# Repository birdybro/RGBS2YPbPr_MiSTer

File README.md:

# RGBS2YPbPr_MiSTer
Just a fun simple external adapter so you don't have to mod your AG620x-based HDMI to VGA Direct video Adapter for YPbPr

I changed the name of the project partway through making it. This is an amateurly designed untested board currently, I'm making a few eventually when boards get here from JLCPCB.

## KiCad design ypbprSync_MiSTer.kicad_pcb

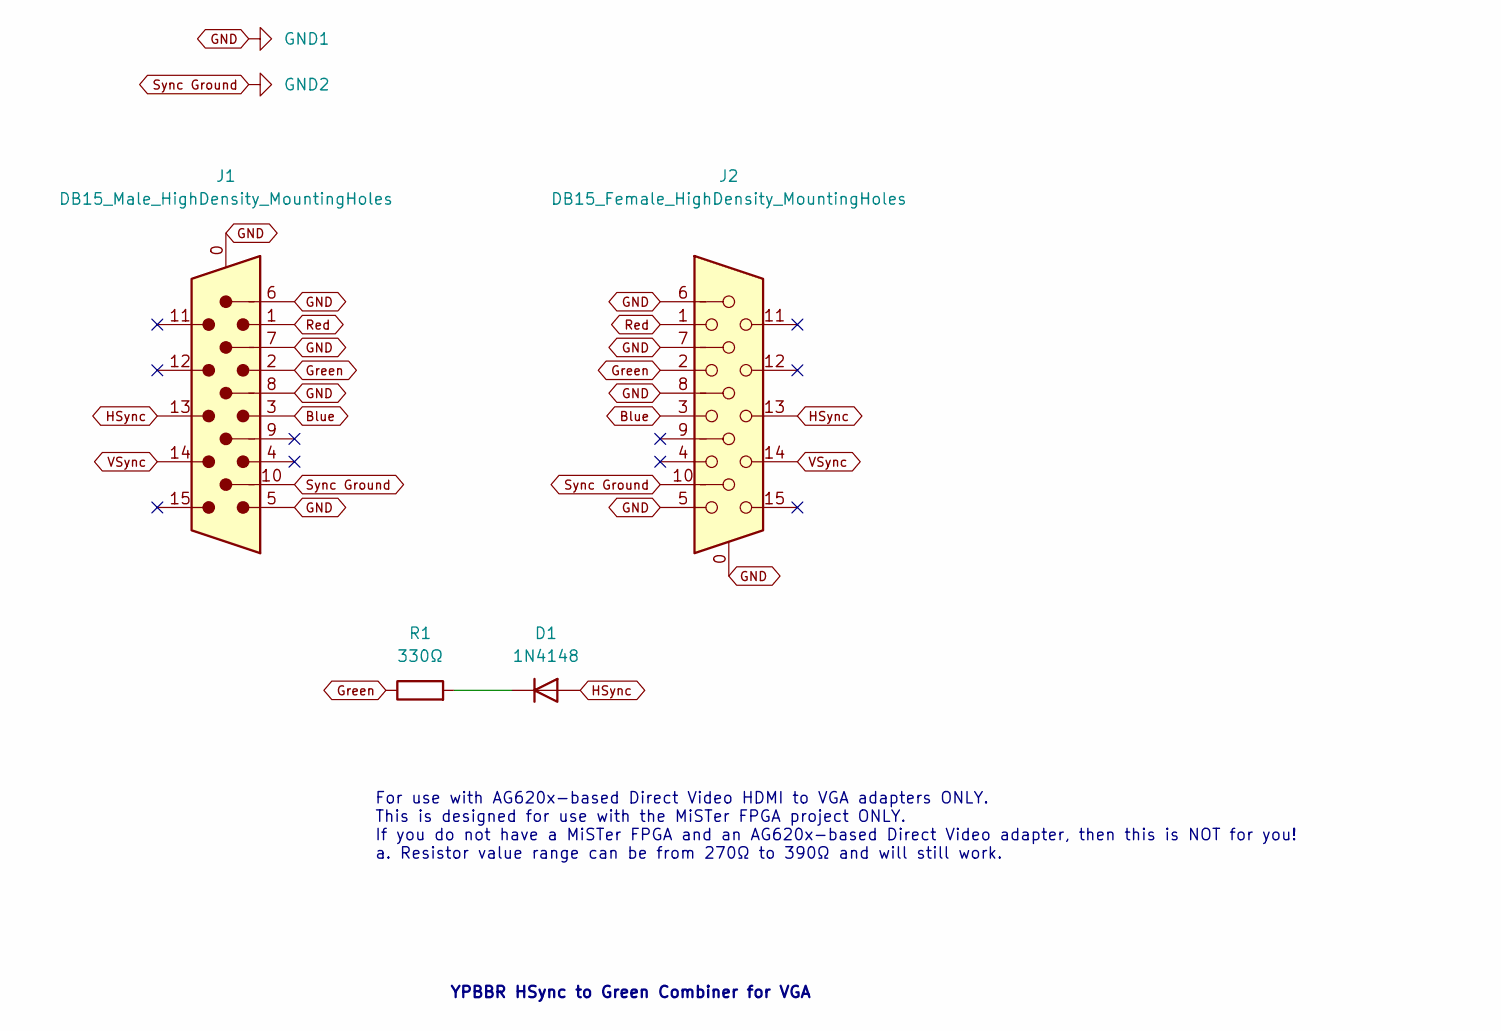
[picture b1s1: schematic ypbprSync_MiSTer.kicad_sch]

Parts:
D1: 1N4148; D_DO-35_SOD27_P7.62mm_Horizontal
J1: DB15_Male_HighDensity_MountingHoles; DSUB-15-HD_Male_Horizontal_P2.29x1.98mm_EdgePinOffset3.03mm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
J2: DB15_Female_HighDensity_MountingHoles; DSUB-15-HD_Female_Horizontal_P2.29x1.98mm_EdgePinOffset3.03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
R1: 330Ω; R_Axial_DIN0207_L6.3mm_D2.5mm_P7.62mm_Horizontal

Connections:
Blue: J1.3, J2.3
GND: J1.0, J1.5, J1.6, J1.7, J1.8, J2.0, J2.5, J2.6, J2.7, J2.8
Green: J1.2, J2.2, R1.1
HSync: D1.2 (A), J1.13, J2.13
unnamed: D1.1 (K), R1.2
Red: J1.1, J2.1
Sync Ground: J1.10, J2.10
VSync: J1.14, J2.14

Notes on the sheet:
For use with AG620x-based Direct Video HDMI to VGA adapters ONLY. This is designed for use with the MiSTer FPGA project ONLY. If you do not have a MiSTer FPGA and an AG620x-based Direct Video adapter, then this is NOT for you! a. Resistor value range can be from 270Ω to 390Ω and will still work.
YPBBR HSync to Green Combiner for VGA

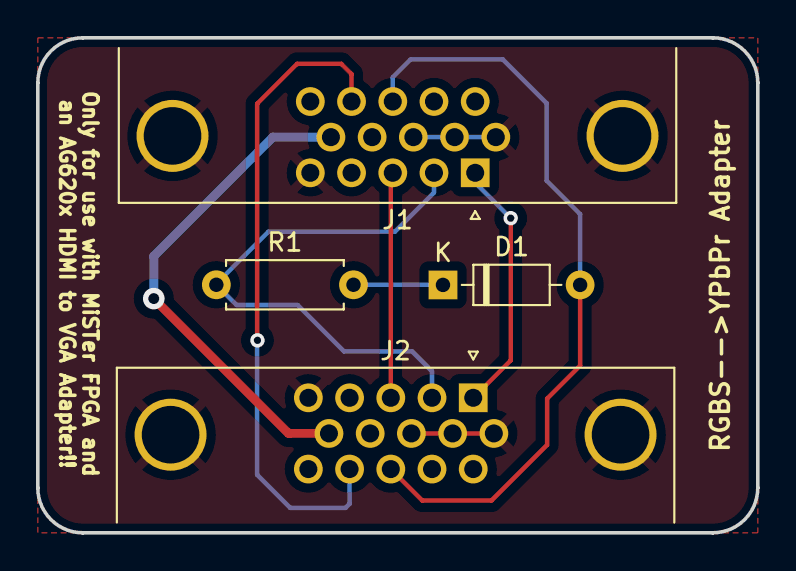
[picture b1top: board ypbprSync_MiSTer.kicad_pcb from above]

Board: 2 copper layers, 40.0 x 27.5 mm, 4 parts (0 on the bottom side), 8 nets.
